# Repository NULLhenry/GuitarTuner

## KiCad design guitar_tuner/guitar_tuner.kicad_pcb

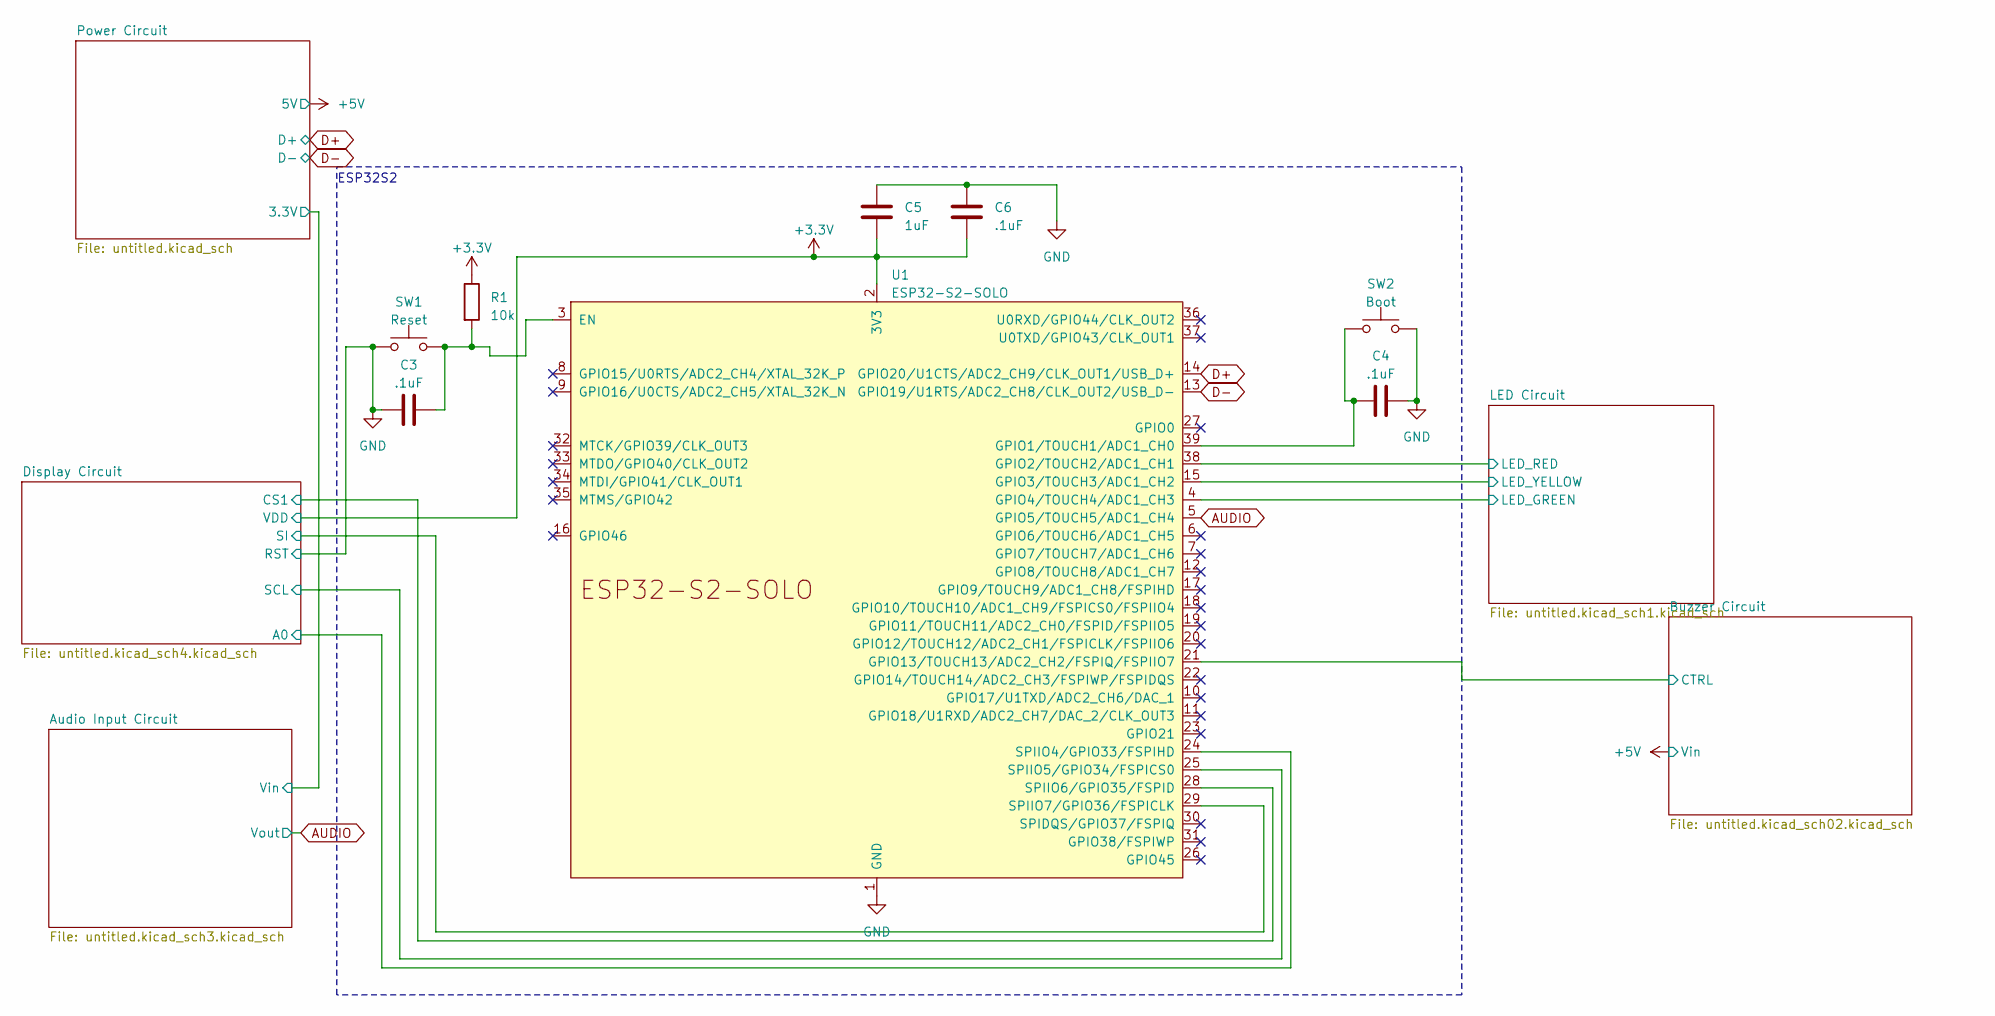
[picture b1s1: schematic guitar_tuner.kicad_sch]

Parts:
C3, C4, C6: .1uF; C_0805_2012Metric_Pad1.18x1.45mm_HandSolder
C5: 1uF; C_0805_2012Metric_Pad1.18x1.45mm_HandSolder
R1: 10k; R_0805_2012Metric_Pad1.20x1.40mm_HandSolder
SW1: Reset; SW_Tactile_SPST_NO_Straight_CK_PTS636Sx25SMTRLFS
SW2: Boot; SW_Tactile_SPST_NO_Straight_CK_PTS636Sx25SMTRLFS
U1: ESP32-S2-SOLO; MOD41_ESP32-S2-SOLO_EXP

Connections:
+3.3V: C5.2, C6.2, R1.1, U1.2 (3V3); also elsewhere on the board
/Buzzer Circuit/CTRL: U1.21 (GPIO13/TOUCH13/ADC2_CH2/FSPIQ/FSPIIO7); also elsewhere on the board
/Display Circuit/A0: U1.24 (SPIIO4/GPIO33/FSPIHD); also elsewhere on the board
/Display Circuit/CS1: U1.28 (SPIIO6/GPIO35/FSPID); also elsewhere on the board
/Display Circuit/SCL: U1.25 (SPIIO5/GPIO34/FSPICS0); also elsewhere on the board
/Display Circuit/SI: U1.29 (SPIIO7/GPIO36/FSPICLK); also elsewhere on the board
/LED Circuit/LED_GREEN: U1.4 (GPIO4/TOUCH4/ADC1_CH3); also elsewhere on the board
/LED Circuit/LED_RED: U1.38 (GPIO2/TOUCH2/ADC1_CH1); also elsewhere on the board
/LED Circuit/LED_YELLOW: U1.15 (GPIO3/TOUCH3/ADC1_CH2); also elsewhere on the board
AUDIO: U1.5 (GPIO5/TOUCH5/ADC1_CH4); also elsewhere on the board
D+: U1.14 (GPIO20/U1CTS/ADC2_CH9/CLK_OUT1/USB_D+); also elsewhere on the board
D-: U1.13 (GPIO19/U1RTS/ADC2_CH8/CLK_OUT2/USB_D-); also elsewhere on the board
GND: C3.1, C4.2, C5.1, C6.1, SW1.1, SW2.2, U1.1 (GND), U1.40 (GND), U1.41 (GND); also elsewhere on the board
unnamed: C3.2, R1.2, SW1.2, U1.3 (EN)
unnamed: C4.1, SW2.1, U1.39 (GPIO1/TOUCH1/ADC1_CH0)

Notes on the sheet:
ESP32S2

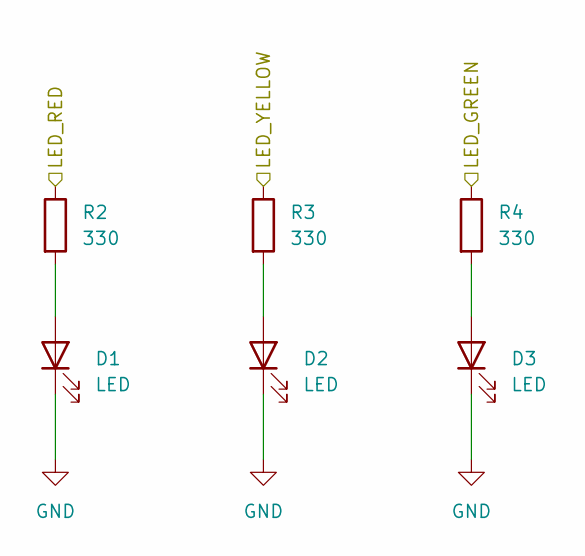
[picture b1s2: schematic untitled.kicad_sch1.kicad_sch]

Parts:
D1, D2, D3: LED; LED_0805_2012Metric_Pad1.15x1.40mm_HandSolder
R2, R3, R4: 330; R_0805_2012Metric_Pad1.20x1.40mm_HandSolder

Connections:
/LED Circuit/LED_GREEN: R4.1; also elsewhere on the board
/LED Circuit/LED_RED: R2.1; also elsewhere on the board
/LED Circuit/LED_YELLOW: R3.1; also elsewhere on the board
GND: D1.1 (K), D2.1 (K), D3.1 (K); also elsewhere on the board
unnamed: D1.2 (A), R2.2
unnamed: D2.2 (A), R3.2
unnamed: D3.2 (A), R4.2

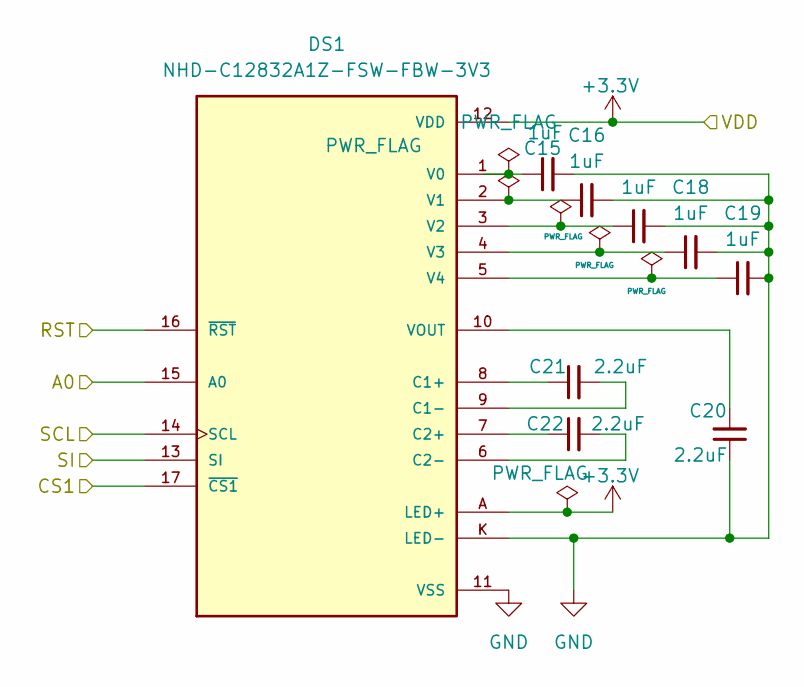
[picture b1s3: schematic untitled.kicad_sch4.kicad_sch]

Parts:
C15, C16, C17, C18, C19: 1uF; C_0805_2012Metric_Pad1.18x1.45mm_HandSolder
C20, C21, C22: 2.2uF; C_0805_2012Metric_Pad1.18x1.45mm_HandSolder
DS1: NHD-C12832A1Z-FSW-FBW-3V3; LCD_NHD-C12832A1Z-FSW-FBW-3V3; PARTREV 7

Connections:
+3.3V: DS1.12 (VDD), DS1.A (LED+); also elsewhere on the board
/Display Circuit/A0: DS1.15 (A0); also elsewhere on the board
/Display Circuit/CS1: DS1.17 (~CS1); also elsewhere on the board
/Display Circuit/SCL: DS1.14 (SCL); also elsewhere on the board
/Display Circuit/SI: DS1.13 (SI); also elsewhere on the board
GND: C15.2, C16.2, C17.2, C18.2, C19.2, C20.1, DS1.11 (VSS), DS1.16 (~RST), DS1.K (LED-); also elsewhere on the board
unnamed: C21.1, DS1.8 (C1+)
unnamed: C21.2, DS1.9 (C1-)
unnamed: C22.1, DS1.7 (C2+)
unnamed: C22.2, DS1.6 (C2-)
unnamed: C15.1, DS1.1 (V0)
unnamed: C16.1, DS1.2 (V1)
unnamed: C17.1, DS1.3 (V2)
unnamed: C18.1, DS1.4 (V3)
unnamed: C19.1, DS1.5 (V4)
unnamed: C20.2, DS1.10 (VOUT)

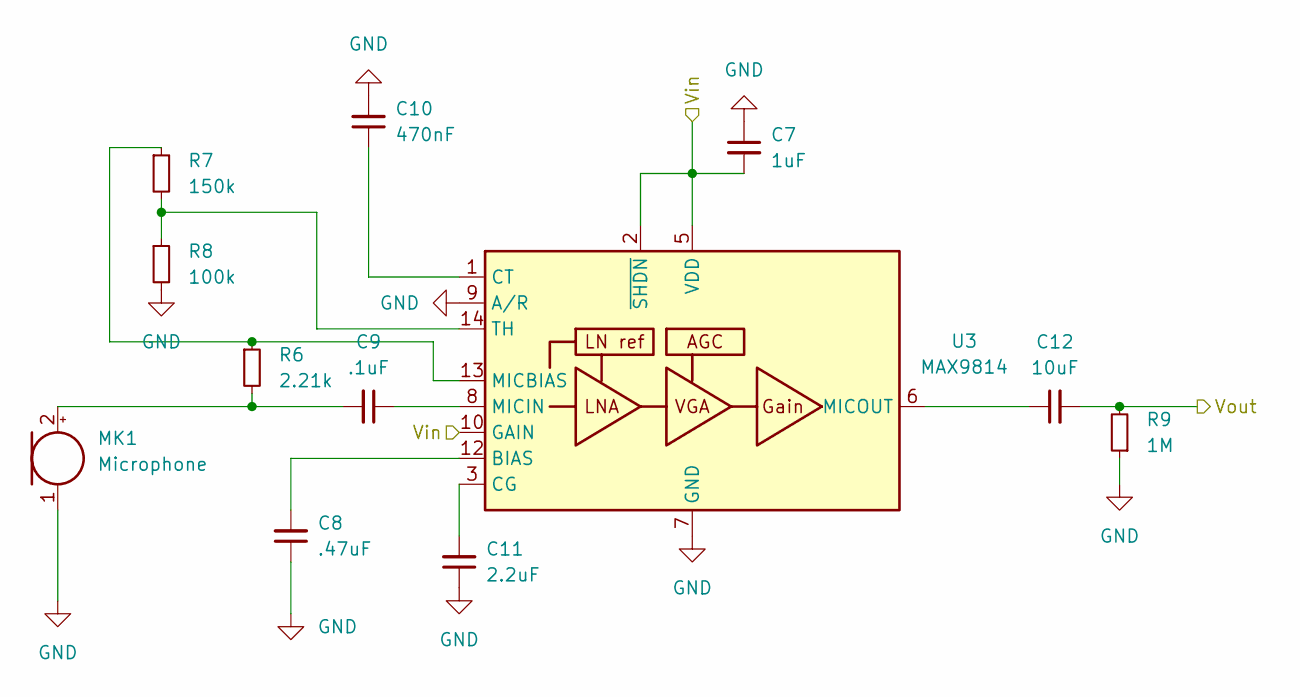
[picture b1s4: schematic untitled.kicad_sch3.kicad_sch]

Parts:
C7: 1uF; C_0805_2012Metric_Pad1.18x1.45mm_HandSolder
C8: .47uF; C_0805_2012Metric_Pad1.18x1.45mm_HandSolder
C9: .1uF; C_0805_2012Metric_Pad1.18x1.45mm_HandSolder
C10: 470nF; C_0805_2012Metric_Pad1.18x1.45mm_HandSolder
C11: 2.2uF; C_0805_2012Metric_Pad1.18x1.45mm_HandSolder
C12: 10uF; C_0805_2012Metric_Pad1.18x1.45mm_HandSolder
MK1: Microphone; L_Axial_L7.0mm_D3.3mm_P2.54mm_Vertical_Fastron_MICC
R6: 2.21k; R_0805_2012Metric_Pad1.20x1.40mm_HandSolder
R7: 150k; R_0805_2012Metric_Pad1.20x1.40mm_HandSolder
R8: 100k; R_0805_2012Metric_Pad1.20x1.40mm_HandSolder
R9: 1M; R_0805_2012Metric_Pad1.20x1.40mm_HandSolder
U3: MAX9814; DFN-14-1EP_3x3mm_P0.4mm_EP1.78x2.35mm

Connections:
/Audio Input Circuit/Vin: C7.2, U3.2 (~SHDN), U3.5 (VDD), U3.10 (GAIN); also elsewhere on the board
AUDIO: C12.2, R9.2; also elsewhere on the board
GND: C7.1, C8.1, C10.2, C11.1, MK1.1 (-), R8.2, R9.1, U3.4 (GND), U3.7 (GND), U3.9 (A/R), U3.11 (GND), U3.15 (GND); also elsewhere on the board
unnamed: C9.2, MK1.2 (+), R6.2
unnamed: C8.2, U3.12 (BIAS)
unnamed: C11.2, U3.3 (CG)
unnamed: C10.1, U3.1 (CT)
unnamed: R6.1, R7.1, U3.13 (MICBIAS)
unnamed: C9.1, U3.8 (MICIN)
unnamed: C12.1, U3.6 (MICOUT)
unnamed: R7.2, R8.1, U3.14 (TH)

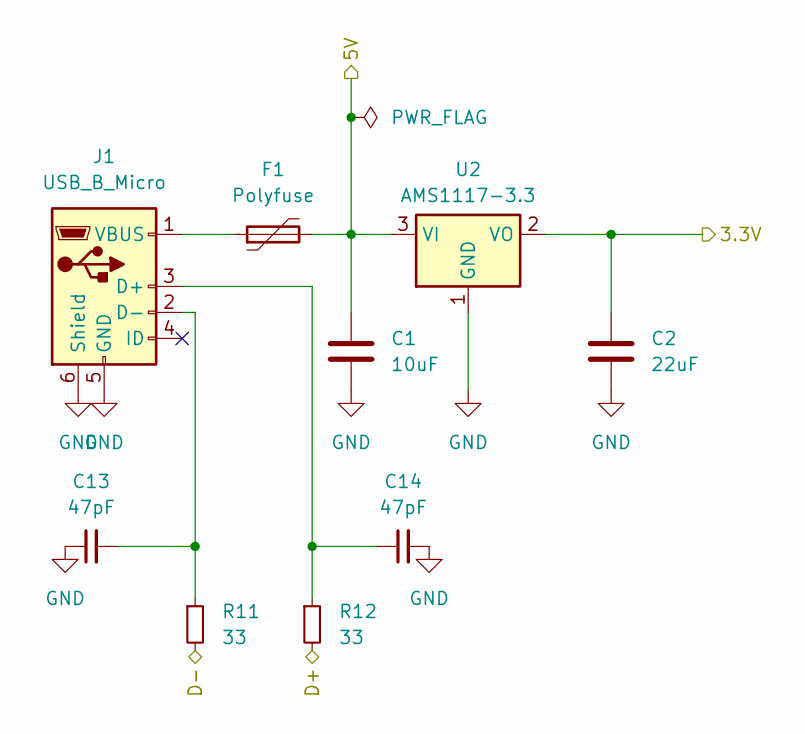
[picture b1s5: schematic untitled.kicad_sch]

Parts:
C1: 10uF; C_0805_2012Metric_Pad1.18x1.45mm_HandSolder
C2: 22uF; C_0805_2012Metric_Pad1.18x1.45mm_HandSolder
C13, C14: 47pF; C_0805_2012Metric_Pad1.18x1.45mm_HandSolder
F1: Polyfuse; Fuse_0805_2012Metric_Pad1.15x1.40mm_HandSolder
J1: USB_B_Micro; USB_Micro-B_Wuerth_629105150521
R11, R12: 33; R_0805_2012Metric_Pad1.20x1.40mm_HandSolder
U2: AMS1117-3.3; SOT-223-3_TabPin2

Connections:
+5V: C1.1, F1.2, U2.3 (VI); also elsewhere on the board
/Audio Input Circuit/Vin: C2.1, U2.2 (VO); also elsewhere on the board
D+: R12.2; also elsewhere on the board
D-: R11.2; also elsewhere on the board
GND: C1.2, C2.2, C13.1, C14.2, J1.5 (GND), J1.6 (Shield), U2.1 (GND); also elsewhere on the board
unnamed: C14.1, J1.3 (D+), R12.1
unnamed: C13.2, J1.2 (D-), R11.1
unnamed: F1.1, J1.1 (VBUS)

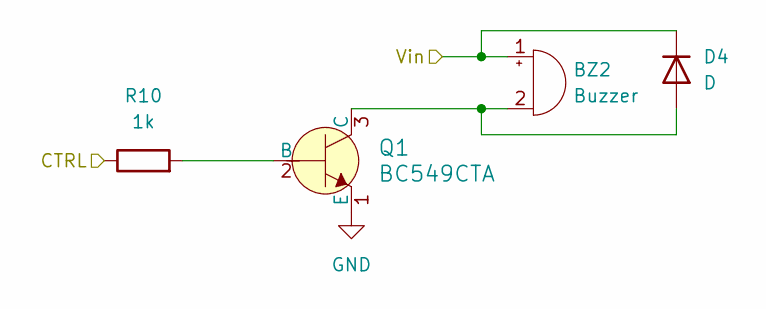
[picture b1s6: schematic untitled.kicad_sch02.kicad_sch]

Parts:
BZ2: Buzzer; Buzzer_12x9.5RM7.6
D4: D; D_0805_2012Metric_Pad1.15x1.40mm_HandSolder
Q1: BC549CTA; SOT-23_Handsoldering; MPN BC549CTA; Digi-Key_PN BC549CTAFSCT-ND
R10: 1k; R_0805_2012Metric_Pad1.20x1.40mm_HandSolder

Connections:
+5V: BZ2.1 (+), D4.1 (K); also elsewhere on the board
/Buzzer Circuit/CTRL: R10.1; also elsewhere on the board
GND: Q1.1 (E); also elsewhere on the board
unnamed: BZ2.2 (-), D4.2 (A), Q1.3 (C)
unnamed: Q1.2 (B), R10.2

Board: 2 copper layers, 48 parts (0 on the bottom side), 43 nets, no tracks yet.

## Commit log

2025-03-13 Added empty project file
2025-03-14 ESP 32
2025-03-14 Made boxes
2025-03-14 ESP32
    ESP32 Addition
2025-03-14 Added micro USB B for input power as well as voltage regulator.
2025-03-15 LED
    Addition of LED Circuits
2025-03-15 Buzzer Circuit
    Transistor and buzzer, have not yet set up power or connected to ESP32
2025-03-15 Buzzer Circuit Pins
2025-03-15 OLED
    Addition of OLED Screen
2025-03-15 Created the audio input circuit, added all passives and assigned values
2025-03-15 AudioHierarchyLabel
    Addition of Labels
2025-03-15 Connected power to buzzer and audio input circuits, made connections to microcontroller.
2025-04-02 Fixed short short with R1 and space out schematic for audio input.
2025-04-02 Multiple Schematic Fixes
    - Created outputs from the power schematic for the D+ and D- pins and attached them to esp
    - Changed net class directives to global labels as net class directives don't properly translate to layout (5V, Audio, 3.3V)
    - Fixed buzzer schematic as the esp was not properly connected to it due to mismatched grid sizes
    - Added power flags to voltage sources
2025-04-02 Screen
    New Screen
2025-04-03 Errors, pins, powerflags
2025-04-03 Quick Edits on Screen Connections
    Quick Update
2025-04-03 quick file rename
2025-04-03 Actual change to buzzer title
2025-04-03 Revert name change
2025-04-03 Edited names of subsheets
2025-04-04 Power Circuit Footprints
2025-04-04 Led Circuit Footprints
2025-04-04 Audio input footprints
2025-04-04 Buzzer Circuit Footprints and New Diode
2025-04-04 Fixed ERC issue with buzzer circuit
2025-04-04 FootprintUpdate
    Upodate to Footprints
2025-04-04 add footprints
    add footprints for display and esp32
2025-04-04 added power flag on power subschematic
    added power flag on power subschematic
2025-04-04 ERC Complete
2025-04-04 ERC Complete
    f
2025-04-04 ERC Check
2025-04-04 Footprint Fix
    I hope
